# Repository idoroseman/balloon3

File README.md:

# balloon3
Israel Space Balloon Team - APRS Tracker

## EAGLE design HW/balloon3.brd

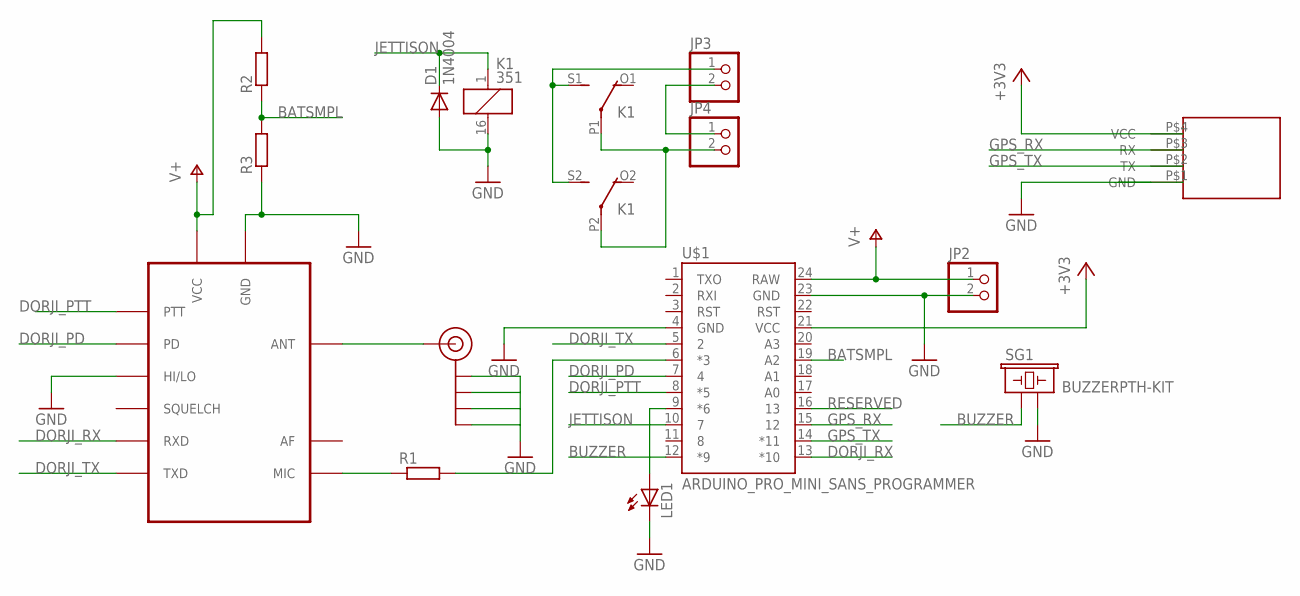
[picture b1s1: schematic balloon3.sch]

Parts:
D1: 1N4004; DO41-10
J$1: SMA_EDGE; SMA-EDGE
JP2, JP3, JP4: PINHD-1X2; 1X02
K1: 351
LED1: LED3MM
R1, R2, R3: R-EU_0204/7; 0204/7
SG1: BUZZERPTH-KIT; BUZZER-12MM-KIT
U$1: ARDUINO_PRO_MINI_SANS_PROGRAMMER; ARDUINO_PRO_MINI
U$2: DORJI
U$3: NEO-6M-MODULE

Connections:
+3V3: U$1.21 (VCC), U$3.P$4 (VCC)
BATSMPL: R2.1, R3.2, U$1.19 (A2)
BUZZER: SG1.+ (1), U$1.12 (*9)
DORJI_PD: U$1.7 (4), U$2.P$6 (PD)
DORJI_PTT: U$1.8 (*5), U$2.P$5 (PTT)
DORJI_RX: U$1.13 (*10), U$2.P$16 (RXD)
DORJI_TX: U$1.5 (2), U$2.P$17 (TXD)
GND: D1.A, J$1.GND@0 (GND), J$1.GND@1 (GND), J$1.GND@2 (GND), J$1.GND@3 (GND), JP2.2, K1.16 (2), LED1.K (C), R3.1, SG1.- (2), U$1.4 (GND), U$1.23 (GND), U$2.P$7 (HI/LO), U$2.P$9 (GND), U$2.P$10 (GND), U$3.P$1 (GND)
GPS_RX: U$1.15 (12), U$3.P$3 (RX)
GPS_TX: U$1.14 (*11), U$3.P$2 (TX)
JETTISON: D1.C, K1.1, U$1.10 (7)
unnamed: R1.2, U$1.6 (*3)
unnamed: R1.1, U$2.P$18 (MIC)
unnamed: J$1.SIG (SIGNAL), U$2.P$12 (ANT)
unnamed: JP4.2, K1.P1, K1.P2
unnamed: LED1.A, U$1.9 (*6)
unnamed: JP3.1, K1.S1 (S), K1.S2 (S)
unnamed: JP3.2, JP4.1
RESERVED: U$1.16 (13)
V+: JP2.1, R2.2, U$1.24 (RAW), U$2.P$8 (VCC)

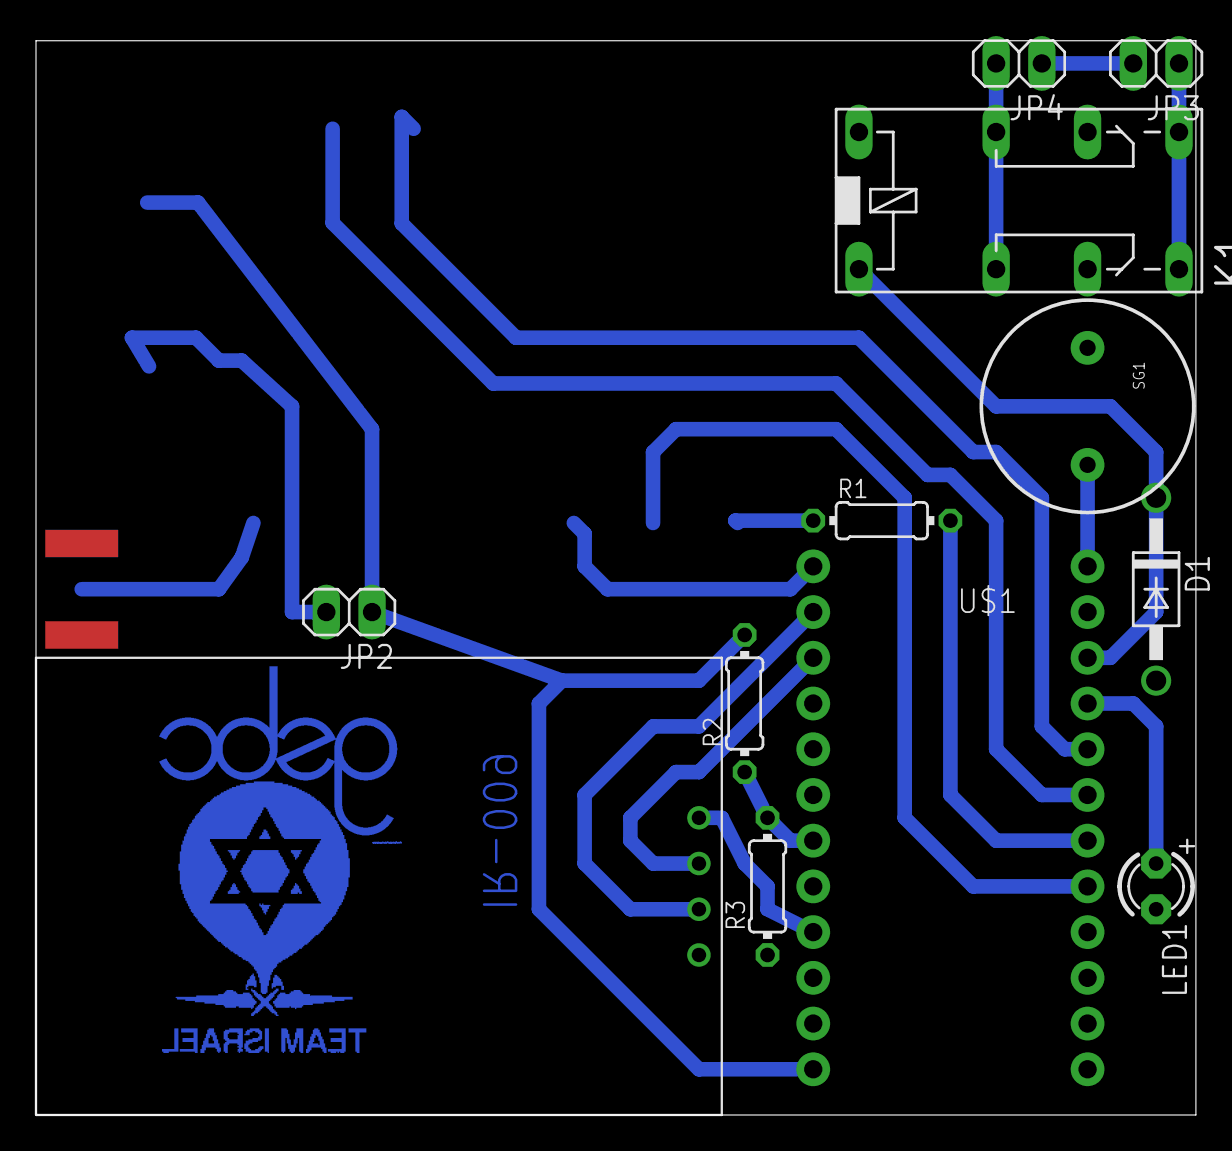
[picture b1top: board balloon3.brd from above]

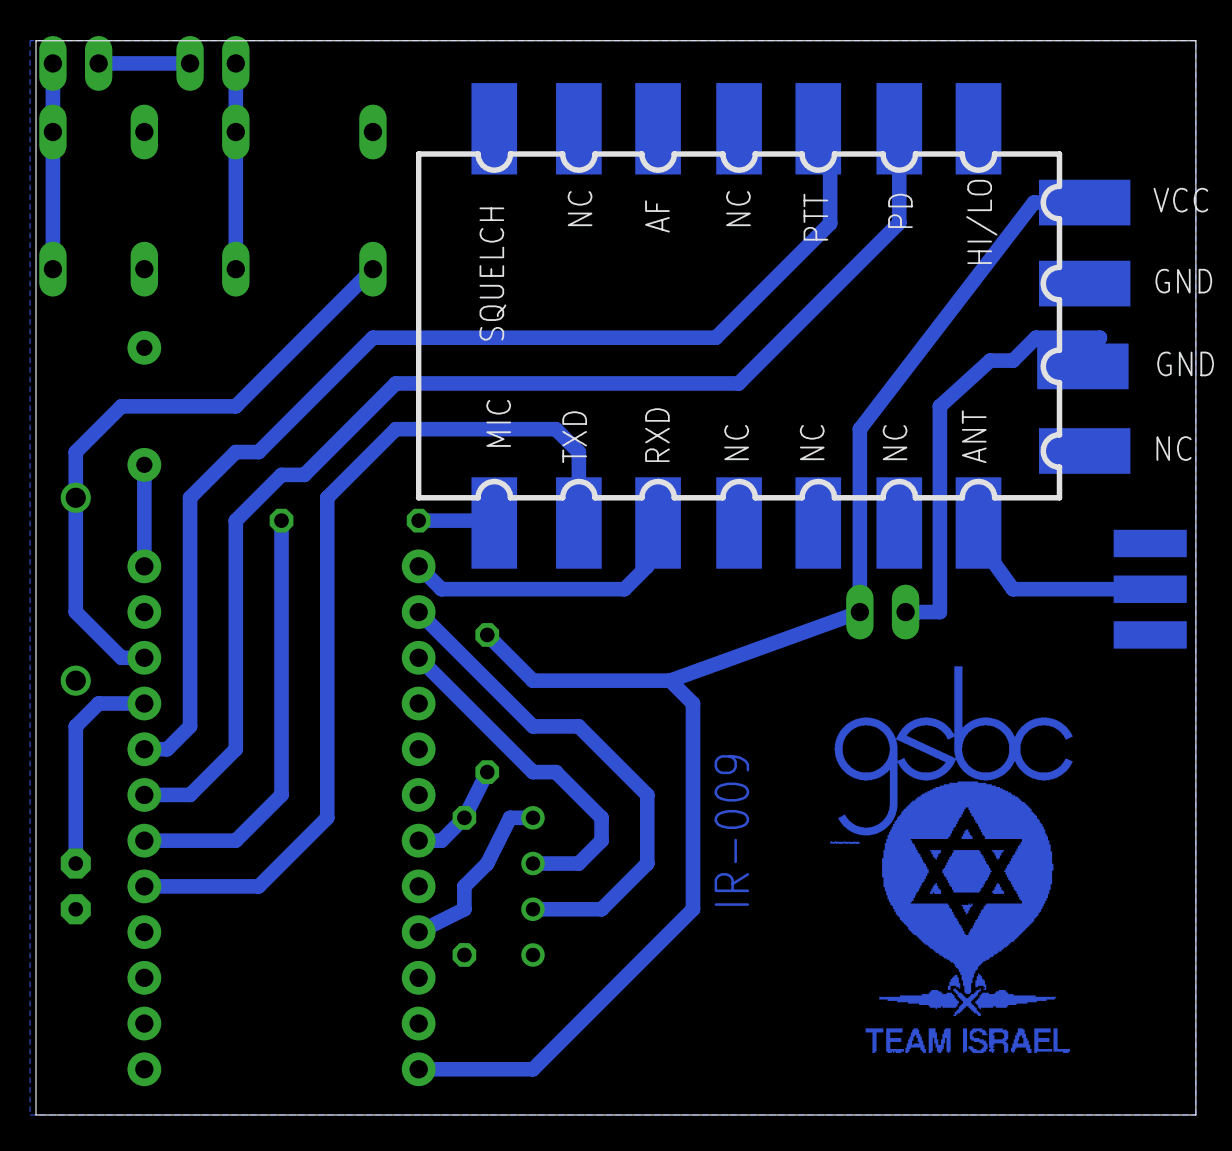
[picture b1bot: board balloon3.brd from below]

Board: 2 copper layers, 64.4 x 59.7 mm, 16 parts (4 on the bottom side), 19 nets.

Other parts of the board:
U$4: GSBC
U$5: TEAMISRAEL

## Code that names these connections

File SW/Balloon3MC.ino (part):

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#include <util/crc16.h>
#include <SoftwareSerial.h>

#define DORJI_RX 2
#define DORJI_TX 10
#define DORJI_PD 4
#define DORJI_PTT 5
#define DORJI_PWM 3

#define RELAY 7
#define BUZZER 9
#define LED 13 
#define LED2 6
#define GPS_RX 11
#define GPS_TX 12

/*
Ganey Tikva
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{
  Serial.begin(9600);
  Serial.print("Welcome to gsbc.il\r\n");
  pinMode(BUZZER,OUTPUT);
  digitalWrite(BUZZER, LOW);
  pinMode(RELAY,OUTPUT);
  digitalWrite(RELAY, LOW);
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void init_dorji()
{
  bool success = false;
  pinMode(DORJI_TX,OUTPUT);
  pinMode(DORJI_PD,OUTPUT);
  pinMode(DORJI_PTT,OUTPUT);
  pinMode(DORJI_PWM,OUTPUT);
  digitalWrite(DORJI_PD, HIGH);   
  digitalWrite(DORJI_PTT, HIGH);   
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
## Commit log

2015-08-17 added hardware and software files

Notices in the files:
parts and their libraries:
SparkFun-Connectors: Licensing: Creative Commons ShareAlike 4.0 International - https://creativecommons.org/licenses/by-sa/4.0
